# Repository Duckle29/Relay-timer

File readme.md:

# Relay Tiemr

This is a simple PCB for controlling a relay and 7segment display from an arduino nano.

The firmware and design isn't tested, but should work. It reads the potentiometer to set the time on the timer, and then on a button push it starts the timer. If you want to reset the timer, then you can hold the button, and it'll enter the setup again once you let go.

At the start of the timer, the relay will be turned on/off depending on the setting in the firmware, and when the timer reaches zero, it'll sound a buzzer, and set the relay back to what it was before starting the timer.

Both the firmware and the PCB is fairly easy to modify, to use whatever MCU you want :)

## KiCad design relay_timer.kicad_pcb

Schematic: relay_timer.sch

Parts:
A1: Arduino_Nano_v3.x; Arduino_Nano
BZ1: Buzzer; Buzzer_12x9.5RM7.6
D1: 1N4007; D_DO-41_SOD81_P10.16mm_Horizontal
J1: Input; TerminalBlock_bornier-3_P5.08mm
J2: Output; TerminalBlock_bornier-3_P5.08mm
K1: DPST FormA; Relay_DPST_Schrack-RT2-FormA_RM5mm
Q1: BSS138; SOT-23_Handsoldering
R1: 10k; R_0603_1608Metric_Pad0.84x1.00mm_HandSolder
RV1: R_POT; PinHeader_1x03_P2.54mm_Vertical
SW1: tactile; SW_TH_Tactile_Omron_B3F-10xx

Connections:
+5V: A1.27, D1.1 (K), K1.A1, RV1.1; also elsewhere on the board
/7seg/P: A1.9; also elsewhere on the board
/7seg/a: A1.5; also elsewhere on the board
/7seg/b: A1.11; also elsewhere on the board
/7seg/c: A1.8; also elsewhere on the board
/7seg/d: A1.10; also elsewhere on the board
/7seg/e: A1.16; also elsewhere on the board
/7seg/f: A1.7; also elsewhere on the board
/7seg/g: A1.15; also elsewhere on the board
/7seg/~CA1: A1.6; also elsewhere on the board
/7seg/~CA2: A1.13; also elsewhere on the board
/7seg/~CA3: A1.12; also elsewhere on the board
/7seg/~CA4: A1.14; also elsewhere on the board
GND: A1.4, A1.29, BZ1.2, Q1.2, R1.2, RV1.3, SW1.3, SW1.4; also elsewhere on the board
unnamed: A1.19, RV1.2
unnamed: A1.21, SW1.1, SW1.2
unnamed: A1.22, BZ1.1
unnamed: D1.2 (A), K1.A2, Q1.3
unnamed: J1.1, K1.11
unnamed: J1.3, K1.21
unnamed: J2.1, K1.24
unnamed: J2.3, K1.14
Relay: A1.20, Q1.1, R1.1

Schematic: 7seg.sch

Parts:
Q2, Q3, Q4, Q5, Q6, Q7, Q8, Q9: BSS138; SOT-23_Handsoldering
Q10, Q11, Q12, Q13: BSS84L; SOT-23_Handsoldering
R2, R3, R4, R5, R6, R7, R8, R9, R18, R19, R20, R21: 10k; R_0603_1608Metric_Pad0.84x1.00mm_HandSolder
R10, R11, R12, R13, R14, R15, R16, R17: 150R; R_0603_1608Metric_Pad0.84x1.00mm_HandSolder
U1: CA56-12SRWA

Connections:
+5V: Q10.2, Q11.2, Q12.2, Q13.2, R18.1, R19.1, R20.1, R21.1; also elsewhere on the board
/7seg/P: Q8.1, R8.1; also elsewhere on the board
/7seg/a: Q3.1, R3.1; also elsewhere on the board
/7seg/b: Q2.1, R2.1; also elsewhere on the board
/7seg/c: Q5.1, R5.1; also elsewhere on the board
/7seg/d: Q4.1, R4.1; also elsewhere on the board
/7seg/e: Q7.1, R7.1; also elsewhere on the board
/7seg/f: Q6.1, R6.1; also elsewhere on the board
/7seg/g: Q9.1, R9.1; also elsewhere on the board
/7seg/~CA1: Q10.1, R18.2; also elsewhere on the board
/7seg/~CA2: Q11.1, R19.2; also elsewhere on the board
/7seg/~CA3: Q12.1, R20.2; also elsewhere on the board
/7seg/~CA4: Q13.1, R21.2; also elsewhere on the board
GND: Q2.2, Q3.2, Q4.2, Q5.2, Q6.2, Q7.2, Q8.2, Q9.2, R2.2, R3.2, R4.2, R5.2, R6.2, R7.2, R8.2, R9.2; also elsewhere on the board
unnamed: Q2.3, R11.2
unnamed: Q3.3, R10.2
unnamed: Q4.3, R13.2
unnamed: Q5.3, R12.2
unnamed: Q6.3, R15.2
unnamed: Q7.3, R14.2
unnamed: Q8.3, R17.2
unnamed: Q9.3, R16.2
unnamed: Q10.3, U1.12
unnamed: Q11.3, U1.9
unnamed: Q12.3, U1.8
unnamed: Q13.3, U1.6
unnamed: R10.1, U1.11
unnamed: R11.1, U1.7
unnamed: R12.1, U1.4
unnamed: R13.1, U1.2
unnamed: R14.1, U1.1
unnamed: R15.1, U1.10
unnamed: R16.1, U1.5
unnamed: R17.1, U1.3

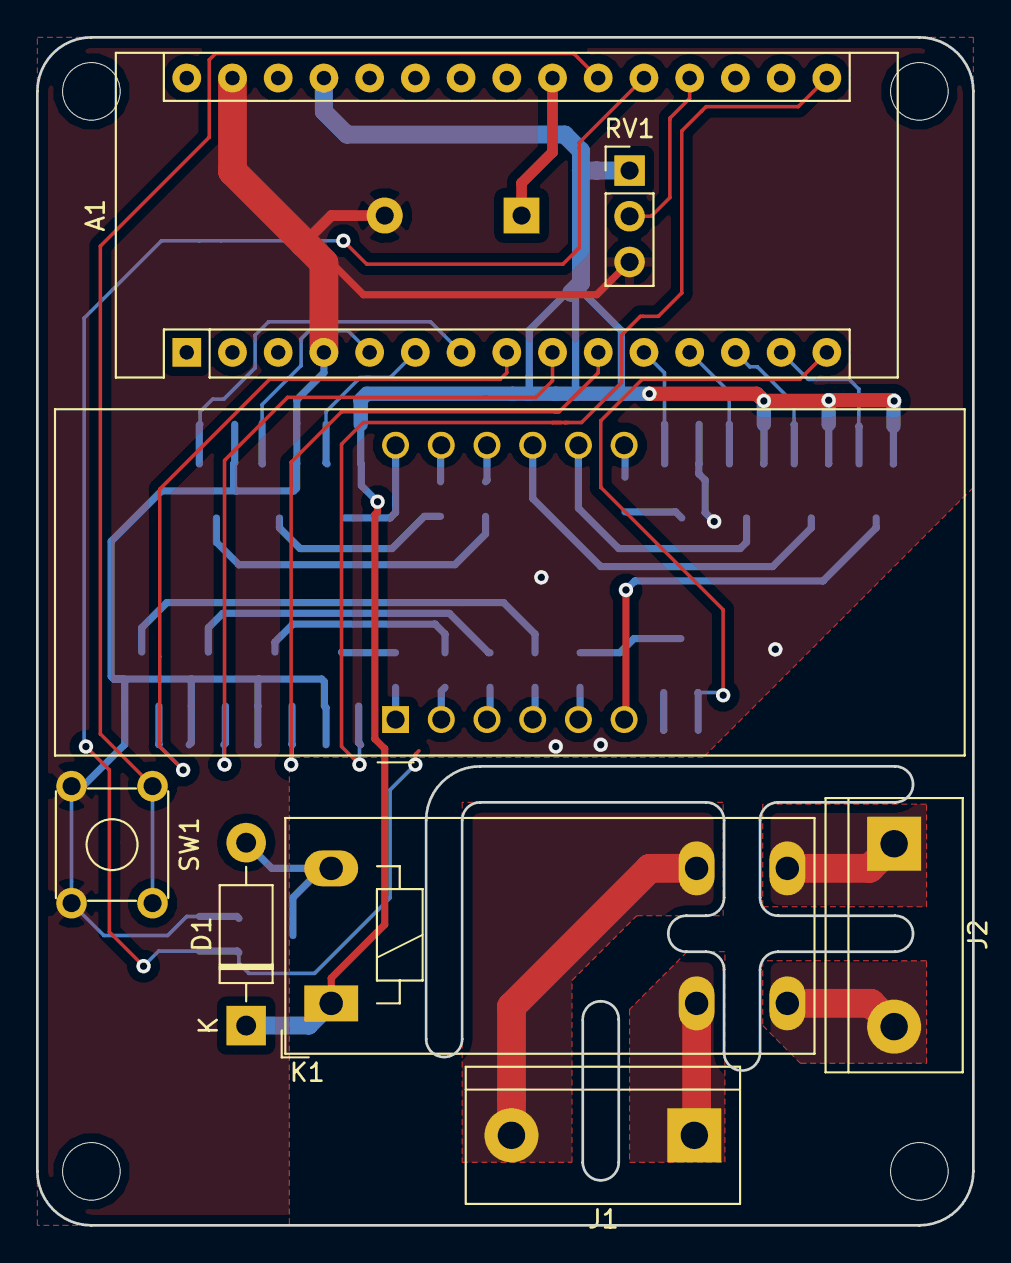
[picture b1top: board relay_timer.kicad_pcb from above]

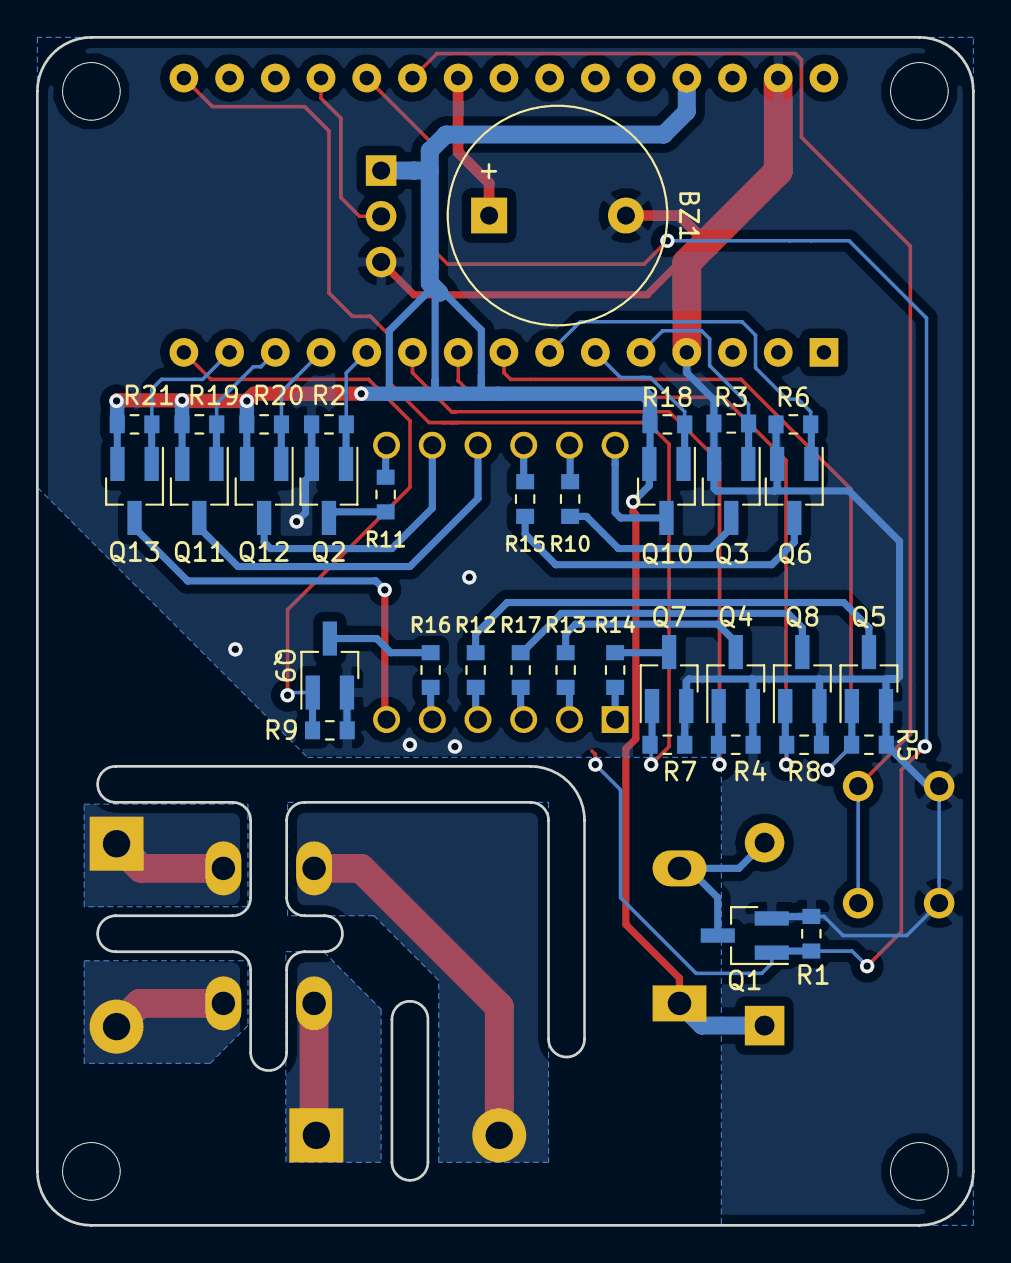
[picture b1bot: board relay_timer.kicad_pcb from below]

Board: 2 copper layers, 52.0 x 66.0 mm, 43 parts (35 on the bottom side), 43 nets.

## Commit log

2018-07-15 Added firmware
2018-07-15 Ignored vscode files, and removed duplicated firmare
2018-07-15 Added Readme
